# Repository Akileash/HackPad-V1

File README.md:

# HackPad V1

This is my custom macro pad project built around the Seeed Studio XIAO RP2040.  
It has a compact 6-key layout, two rotary encoders, a 0.91" OLED, and RGB lighting.

## Features

- 6 MX-style mechanical switches
- 2 EC11 rotary encoders
- 0.91" I2C OLED display (128x32)
- 6 SK6812 MINI-E RGB LEDs
- Custom 2-layer PCB designed in KiCad
- Custom case designed in CAD
- KMK-based firmware configuration

## Project Images

### Overall HackPad

### Parts

### PCB

### Schematics

## Bill of Materials (BOM)

| Item | Quantity | Description |
| :--- | :---: | :--- |
| MCU | 1 | Seeed Studio XIAO RP2040 (Unsoldered) |
| Switches | 6 | MX-Style Mechanical Switches |
| Keycaps | 6 | White Blank DSA Profile Keycaps |
| Encoders | 2 | EC11 Rotary Encoders |
| OLED Display | 1 | 0.91" I2C OLED (Pinout: GND-VCC-SCL-SDA) |
| Diodes | 8 | 1N4148 Through-hole Diodes |
| LEDs | 6 | SK6812 MINI-E RGB NeoPixels |
| Screws | 4 | M3x16mm Socket Head Cap Screws |
| Inserts | 4 | M3 Brass Heat-Set Inserts (5mm OD, 4mm Length) |
| PCB | 1 | Custom 2-Layer Hackpad PCB |
| Feet | 4 | Adhesive rubber bumpons (screw size may be 3x20 if needed) |

## Firmware

Firmware is in `Firmware/main.py`. Right now it is set up for:

- 6-key macro layout
- dual encoder input
- OLED output
- onboard RGB effects

## Repository Structure

- `Firmware/` - KMK firmware
- `PCB/` - KiCad files
- `CAD/` - complete CAD model
- `Production/Case/` - case production parts
- `Media/` - README images

## Notes

Images used in this README are stored in `Media/`:

- `MainPic.png`
- `Parts.png`
- `PCB.png`
- `Schematic1.png`
- `Schematic2.png`
- `Schematic3.png`

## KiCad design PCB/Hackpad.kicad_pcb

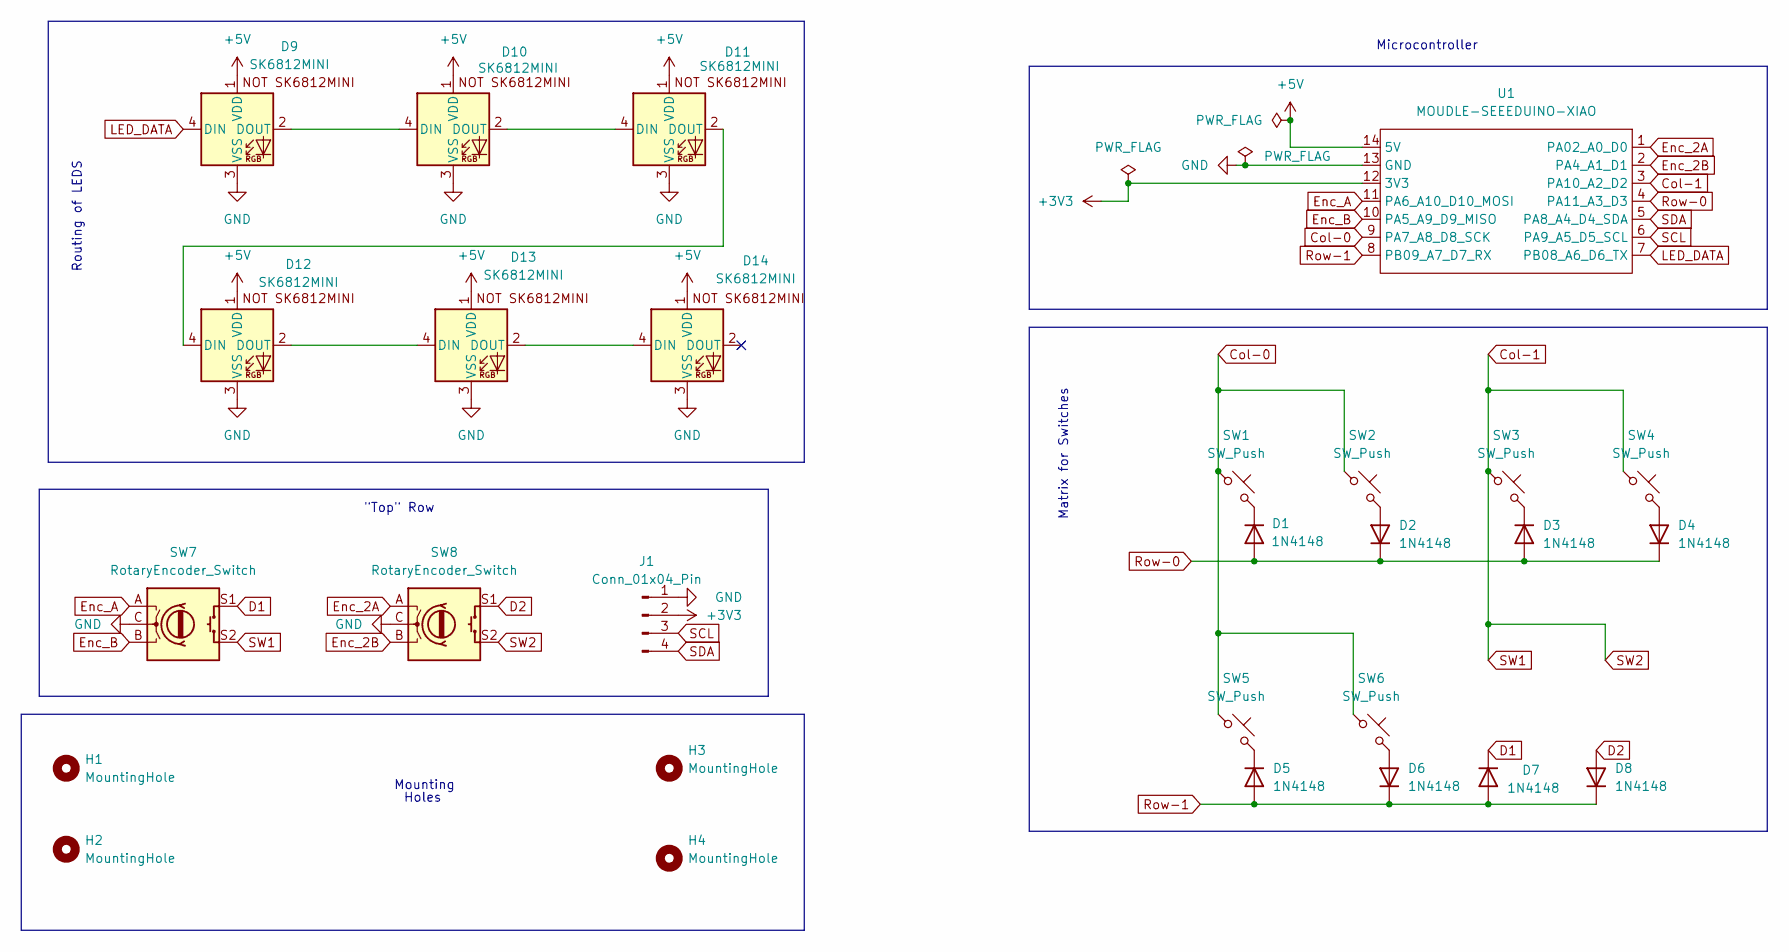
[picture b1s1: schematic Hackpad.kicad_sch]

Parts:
D1, D2, D3, D4, D5, D6, D7, D8: 1N4148; D_DO-35_SOD27_P7.62mm_Horizontal
D9, D10, D11, D12, D13, D14: SK6812MINI; MX_SK6812MINI-E_REV
H1, H2, H3, H4: MountingHole; MountingHole_3.2mm_M3
J1: Conn_01x04_Pin; SSD1306-0.91-OLED-4pin-128x32
SW1, SW2, SW3, SW4, SW5, SW6: SW_Push; SW_Cherry_MX_1.00u_PCB
SW7, SW8: RotaryEncoder_Switch; RotaryEncoder_Alps_EC11E-Switch_Vertical_H20mm
U1: MOUDLE-SEEEDUINO-XIAO; XIAO-Generic-Hybrid-14P-2.54-21X17.8MM

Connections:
+3V3: J1.2, U1.12 (3V3)
+5V: D9.1 (VDD), D10.1 (VDD), D11.1 (VDD), D12.1 (VDD), D13.1 (VDD), D14.1 (VDD), U1.14 (5V)
Col-0: SW1.1, SW2.1, SW5.1, SW6.1, U1.9 (PA7_A8_D8_SCK)
Col-1: SW3.1, SW4.1, SW7.S2, SW8.S2, U1.3 (PA10_A2_D2)
D1: D7.1 (K), SW7.S1
D2: D8.2 (A), SW8.S1
Enc_2A: SW8.A, U1.1 (PA02_A0_D0)
Enc_2B: SW8.B, U1.2 (PA4_A1_D1)
Enc_A: SW7.A, U1.11 (PA6_A10_D10_MOSI)
Enc_B: SW7.B, U1.10 (PA5_A9_D9_MISO)
GND: D9.3 (VSS), D10.3 (VSS), D11.3 (VSS), D12.3 (VSS), D13.3 (VSS), D14.3 (VSS), J1.1, SW7.C, SW8.C, U1.13 (GND)
LED_DATA: D9.4 (DIN), U1.7 (PB08_A6_D6_TX)
unnamed: D1.1 (K), SW1.2
unnamed: D2.2 (A), SW2.2
unnamed: D3.1 (K), SW3.2
unnamed: D4.2 (A), SW4.2
unnamed: D5.1 (K), SW5.2
unnamed: D6.2 (A), SW6.2
unnamed: D9.2 (DOUT), D10.4 (DIN)
unnamed: D10.2 (DOUT), D11.4 (DIN)
unnamed: D11.2 (DOUT), D12.4 (DIN)
unnamed: D12.2 (DOUT), D13.4 (DIN)
unnamed: D13.2 (DOUT), D14.4 (DIN)
Row-0: D1.2 (A), D2.1 (K), D3.2 (A), D4.1 (K), U1.4 (PA11_A3_D3)
Row-1: D5.2 (A), D6.1 (K), D7.2 (A), D8.1 (K), U1.8 (PB09_A7_D7_RX)
SCL: J1.3, U1.6 (PA9_A5_D5_SCL)
SDA: J1.4, U1.5 (PA8_A4_D4_SDA)

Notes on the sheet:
Mounting
Microcontroller
Matrix for Switches
Routing of LEDS
Holes
"Top" Row

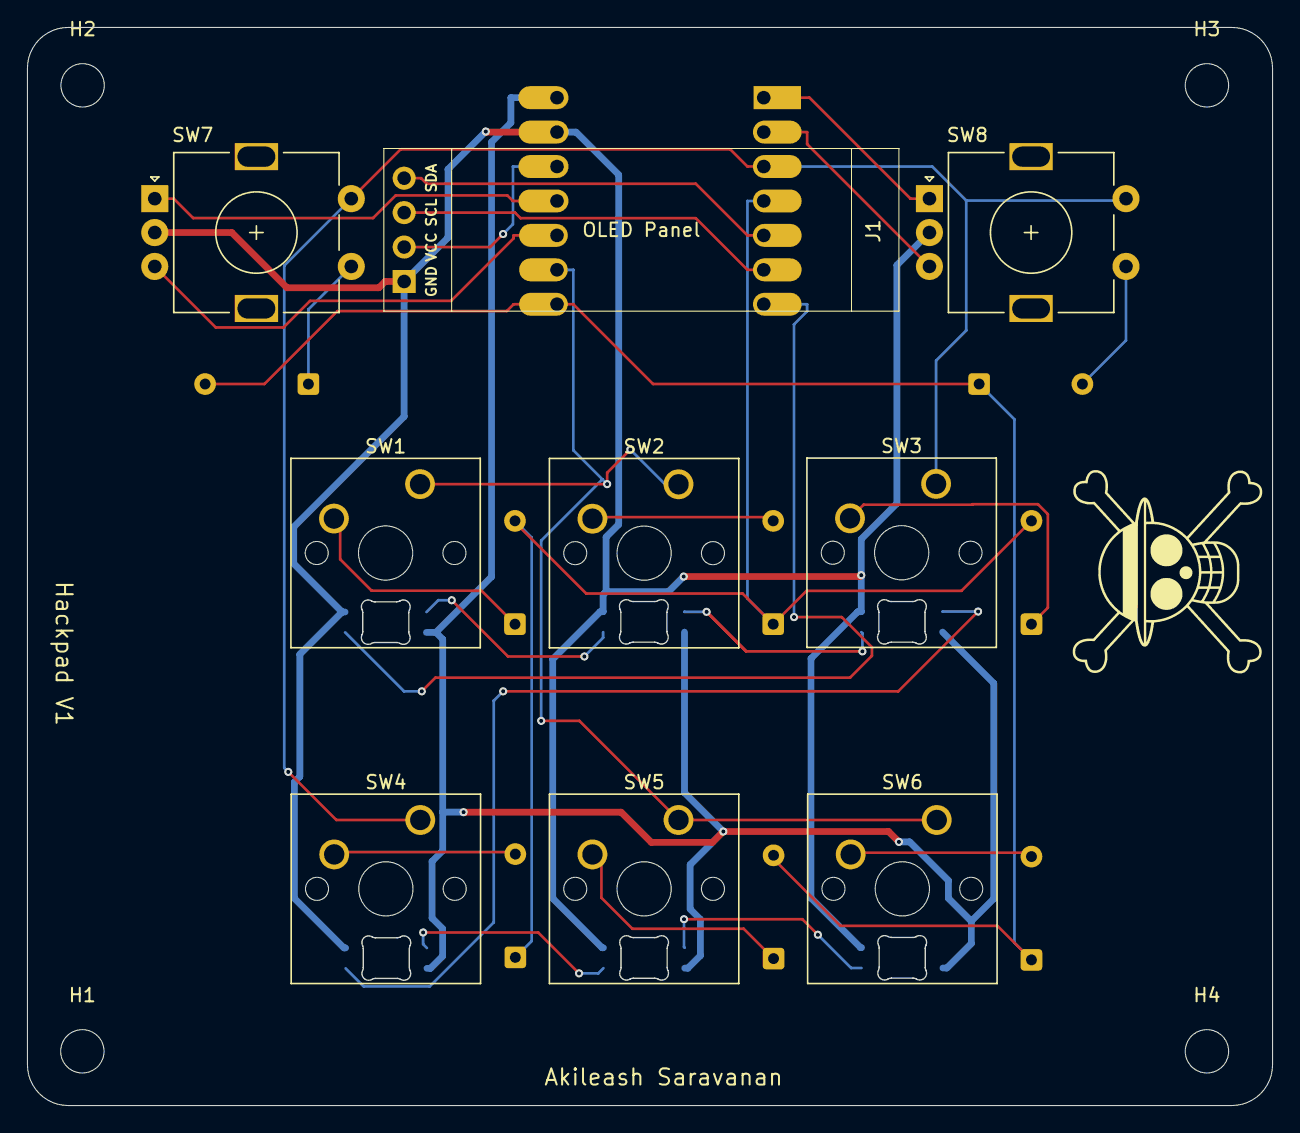
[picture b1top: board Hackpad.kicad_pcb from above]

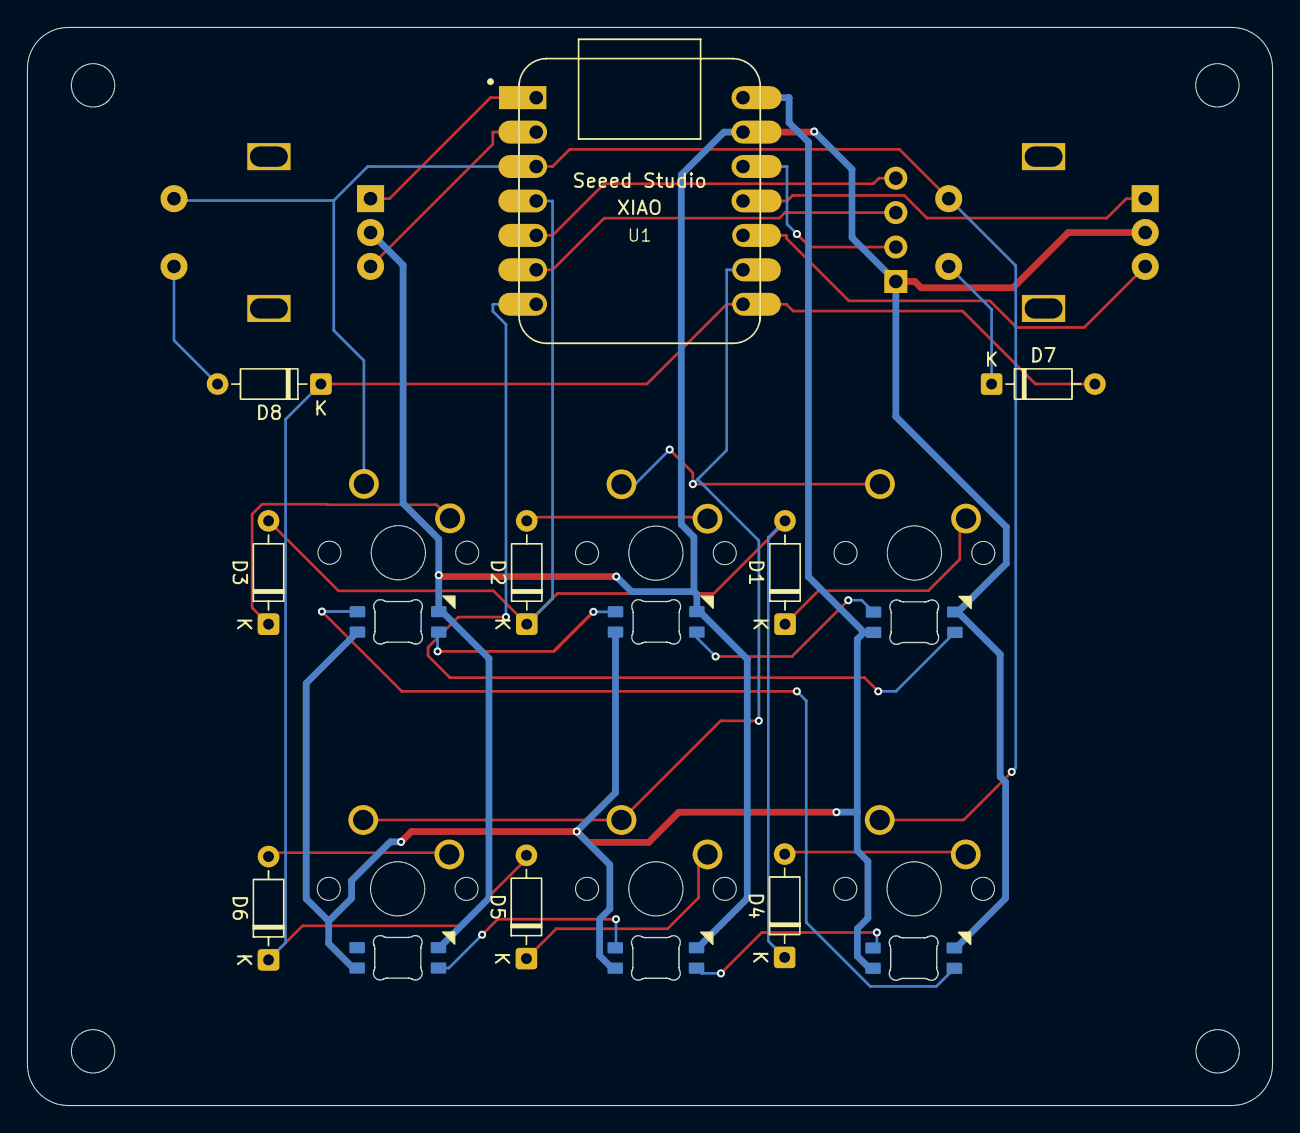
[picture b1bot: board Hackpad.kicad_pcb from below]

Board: 2 copper layers, 91.8 x 79.5 mm, 28 parts (9 on the bottom side), 27 nets.

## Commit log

2026-04-01 Initial HackPad V1 project setup.
    Add firmware, PCB/CAD files, production assets, Media images, and a clean README with project overview and BOM.
2026-04-01 Add production firmware entrypoint.
    Include a copy of KMK main.py in Production/ to satisfy submission packaging requirements.
